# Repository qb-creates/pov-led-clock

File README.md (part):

# Persistence of Vision (POV) Clock

A propeller display that projects an image of an analog clock using a single row of LEDs. The display utilizes an ATmega32 microcontroller two 16-channel LED drivers, and a brushless DC motor.

- Project Video (YouTube): https://youtu.be/6KemDWqXEEw?si=eYfT2QDL8WkOBApL
- Persistance of Vision: https://en.wikipedia.org/wiki/Persistence_of_vision

 <div align="center">
     <!--    -->
    <!--  -->
    
 </div>

<h2> Table of Contents</h2>

1. [Software Used](#software)
2. [ESC Driver Circuit](#escdriver)
    - [PWM Overview](#escpwm)
    - [Parts List](#escpartslist) 
3. [Clock Circuit](#clockcircuit)
    - [LED Driver](#leddriver)
    - [Timer Overview](#clocktimer) 
    - [Parts List](#clockpartslist) 
4. [Power Consumption](#powerconsumption)
5. [Schematics](#schematics)
    - [ESC Driver Schematic](#escschematic)
    - [Clock Schematic](#clockschematic)
6. [STL Viewer](#stlviewer)
    - [Case Base](#casebase)
    - [Case Top](#casetop)

## 1. Software Used
- VSCode with PlatformIO extension: https://docs.platformio.org/en/latest/what-is-platformio.html
- AVRDUDE (Flash Uploader): https://github.com/avrdudes/avrdude
- KiCad (PCB Design): https://www.kicad.org
- AutoDesk Fusion 360 Personal (Case Design): https://www.autodesk.com/products/fusion-360/personal

## 2. ESC Driver Circuit
The ATtiny861 produces a PWM output that is used to drive the ESC (Electronic Speed Controller). A push button connected to PINA7 is used to adjust the duty cycle of the PWM signal.
By adjusting the duty cycle of the PWM signal to a percentage where the output is high for 1ms or less, the motor can be stopped. The push button can be pressed once to start the motor. It can be pressed
again to stop the motor. Button debouncing is accomplished in software by using a 300ms delay after detecting the first low output on the pin. The IR transmitter is used to notify
the clock circuit that it has rotated back to it's starting position. The clock circuit will start projecting the image again after it has rotated back to it's starting position. 
The inductive transmitter is  be mounted to the case while the receiver is mounted to the motor. It is connected to the clock circuit. The ESC's UBEC supplies the ATtiny, IR transmitter, 
and inductive transmitter with power (5V 3A).
<div align="center">
 <div>

 </div>
</div>

### PWM Overview
The PWM frequency is configured to be 500 Hz. The time high for a 100% duty cycle will be 2ms. Usually a 1ms pulse translates to 0% throttle and a 2ms pulse translates to 100% throttle. 
The duty cycle of the PWM signal can be adjusted by setting the Timer's OCRn register to a value between 0 and 255. Every value between 128 and 255 can be used for OCRnB without exceeding 2ms. This allows more wiggle when setting the speed of the motor instead of going from 0% throttle to 100% immediately. Calculation to find the neccessary prescaler value is shown below.

PWM Frequency Equation for ATtiny861
- PWM Frequency = fck / (prescaler * 255)
   
Variables
- fck = 16 Mhz
- Target PWM Frequency = 500 Hz
- prescaler = ?
  
Solve for prescaler
- prescaler = fck / (Target PWM Frequency * 255)
- prescaler = 16 Mhz / (500 Hz * 255)
- prescaler = 125.5 round to 128

Solve for Actual PWM Frequency
- Actual PWM Frequency = 16 Mhz / (128 * 255)
- Actual PWM Frequency = 490 Hz
---
### Parts List
|_**Part Number**_|_**Quantity**_|
|:-----|:--------:|
|<a href="https://www.digikey.com/en/products/detail/microchip-technology/ATTINY861-20PU/1245922">ATtiny861-20PU</a>| x1 |
|<a href="https://www.digikey.com/en/products/filter/rectangular-connectors/headers-male-pins/314">ISP Header</a>| x1 |
|<a href="https://www.digikey.com/en/products/filter/ceramic-capacitors/60">22pF Capacitor</a>| x2 |
|<a href="https://www.digikey.com/en/products/filter/ceramic-capacitors/60">100nF Capacitor</a>| x1 |
|<a href="https://www.digikey.com/en/products/filter/oscillators/172">16Mhz Crystal</a>| x1 |
|<a href="https://www.digikey.com/en/products/filter/through-hole-resistors/53">10K resistor</a>| x1 |
|<a href="https://www.digikey.com/en/products/filter/through-hole-resistors/53">330 resistor</a>| x1 |
|<a href="https://www.digikey.com/en/products/filter/diodes/rectifiers/single-diodes/280">1n4148 Diode</a>| x1 |
|<a href="https://www.digikey.com/en/products/detail/e-switch/RP3502ABLK/280446?s=N4IgTCBcDaIKIHECMBOADGgtAOQCIgF0BfIA">Push Button</a>| x1 |
|<a href="https://www.digikey.com/en/products/filter/rectangular-connectors/headers-male-pins/314">Pcb Board 4cm x 6cm</a>| x1 |
|<a href="https://www.amazon.com/gp/product/B08CRTR7CZ/ref=ppx_yo_dt_b_asin_title_o00_s00?ie=UTF8&psc=1">Brushless Motor</a>| x1 |
|<a href="https://www.amazon.com/gp/product/B09H5L3KN5/ref=ppx_yo_dt_b_asin_title_o02_s00?ie=UTF8&psc=1">Barrel Jack</a>| x1 |
|<a href="https://www.sparkfun.com/products/18772">Infrared Emitter</a>| x1 ||
|<a href="https://www.amazon.com/gp/product/B071GRSFBD/ref=ppx_yo_dt_b_asin_title_o03_s00?ie=UTF8&psc=1">ESC 3A UBEC</a>| x1 |
|<a href="https://www.amazon.com/Adapter-Regulated-Switching-Interchangeable-Equipment/dp/B0BFPXZ7S1/ref=sr_1_3_sspa?crid=396GU23EXCZA8&keywords=9v+power+supply&qid=1697854150&sprefix=9v+power%2Caps%2C93&sr=8-3-spons&sp_csd=d2lkZ2V0TmFtZT1zcF9hdGY&psc=1">9V 1A Power Supply</a>| x1 |
|<a href="https://www.adafruit.com/product/1407">5V 200mA Inductive Charging Set </a>| x1 |

## 3. Clock Circuit 
 This circuit projects the image of an anolog clock using of Persistence of Vision.
 The circuit is mounted to a brushless motor and will project the image of the clock everytime the
 motor completes a full rotation. An IR Detector connected to External Interrupt 0 is used to notify 
 the circuit that a full rotation of the motor has occured and that it is back at it's starting position. 
 A 2 second CTC timer is used to add one second to the clock on each CTC compare interrupt. This interrupt is 
 triggered every 1 second. Two 16 channel LED drivers are used to drive the LEDs. Communication with the LED drivers is done using the SPI protocol.
<div align="center">

</div>

### LED Drivers 
The LED Drivers are chained together. Each driver must receive two bytes of data to control their 16 output channels. Four bytes of data must be sent to the first driver in order to control all 32 output channels. The LEDs are mounted in order (starting from the center of the PCB) from 1 to 32. The table below shows which output channel each LED is connected to. 

|_**STP16CPC05 1 Outputs**_|LED Number|--|_**STP16CPC05 2 Outputs**_|LED Number|
|:--:|:--:|:--:|:--:|:--:|
|**Byte0**||--|**Byte2**||
|Out0|LED1|--|Out0|LED17|
|Out1|LED2|--|Out1|LED18|
|Out2|LED3|--|Out2|LED19|
|Out3|LED4|--|Out3|LED20|
|Out4|LED5|--|Out4|LED21|
|Out5|LED6|--|Out5|LED22|
|Out6|LED7|--|Out6|LED23|
|Out7|LED8|--|Out7|LED24|
|||--|||
|**Byte1**||--|**Byte3**||
|Out8|LED16|--|Out8|LED32|
|Out9|LED15|--|Out9|LED31|
|Out10|LED14|--|Out10|LED30|
|Out11|LED13|--|Out11|LED29|
|Out12|LED12|--|Out12|LED28|
|Out13|LED11|--|Out13|LED27|
|Out14|LED10|--|Out14|LED26|
|Out15|LED9|--|Out15|LED25|

Because the LED Drivers are daisy chained together, the data must be transmitted in the following order.
* Byte3 (MSB transmitted first) 
* Byte2 (LSB transmitted first) 
* Byte1 (MSB transmitted first) 
* Byte0 (LSB transmitted first) 
---
### Timer Overview 
A one second timer is configured to update the seconds hand of the clock. The timer is configured to operate in Clear Timer on Compare Match Mode (CTC). A CTC frequency of 0.5 Hz (2s) is required. 
This will trigger the compare match interrupt every second. Because the weight of the crystal caused the ciruit to be unbalanced, it was discarded and the ATmega32's internal 8 Mhz 
oscillator is used instead. Calculation to find the appropriate OCRn values is shown below.

CTC Waveform Frequency Equation
- Frequency = fck / (2 * prescaler * (1 + OCRnA)).

Variables
- Frequency = 0.5Hz = 2 seconds
- fck = 8 Mhz
- prescaler = 256
- OCRnA = ?

Rearranged formula to solve for OCRnA:
- OCRnA = (fck / (2 * prescaler * Frequency)) - 1

Solve for OCRnA
- OCRnA = (8 Mhz / (2 * 256 * 0.5Hz)) - 1 
- OCRnA = 31249
---
### Parts List 
|_**Part Number**_|_**Quantity**_|
|:-----|:--------:|
|<a href="https://www.mouser.com/ProductDetail/Microchip-Technology/ATMEGA32A-AU?qs=6WoM%2FY8vMbbFYDtovr%252BQ5Q%3D%3D">ATmega32A-AU</a>| x1 |
|<a href="https://www.digikey.com/en/products/filter/rectangular-connectors/headers-male-pins/314">ISP Header</a>| x1 |
|<a href="https://www.digikey.com/en/products/detail/jst-sales-america-inc/S2B-PH-SM4-TB/926655?s=N4IgTCBcDaICwFYEFoCMB2OBONyByAIiALoC%2BQA">JST Connector</a>| x1 |
|<a href="https://www.digikey.com/en/products/detail/stmicroelectronics/STP16CPC05MTR/2021162">STP16CPC05MTR LED Driver</a>| x2 |
|<a href="https://www.digikey.com/en/products/filter/led-indication-discrete/105">SMD Led 1205 (3216 Metric)</a>| x32 |
|<a href="https://www.digikey.com/en/products/filter/oscillators/172">16Mhz Crystal</a>| x1 |
|<a href="https://www.digikey.com/en/products/filter/ceramic-capacitors/60">22pF Capacitor 0603 (1608 Metric)</a>| x2 |
|<a href="https://www.digikey.com/en/products/filter/ceramic-capacitors/60">100nF Capacitor 0603 (1608 Metric)</a>| x1 |
|<a href="https://www.digikey.com/en/products/filter/through-hole-resistors/53">10K Resistor 0603 (1608 Metric)</a>| x2 |
|<a href="https://www.digikey.com/en/products/filter/through-hole-resistors/53">7.32K Resistor 0603 (1608 Metric)</a>| x2 |
|<a href="https://www.digikey.com/en/products/filter/diodes/rectifiers/single-diodes/280">1n4148 Diode</a>| x1 |
|<a href="https://www.sparkfun.com/products/19018">Infrared Detector</a>| x1 |

## 4. Power Consumption 
|_**Test Condition**_|_**Power Consumption**_|
|:--|:--:|
|Clock circuit with all LEDs powered on. LEDs are supplied with 3mA each.|120mA|
|Motor running with the weight of the clock circuit|150mA|
|Inductive charging set|100mA|
|Motor running with all LEDs powered on|380mA|

The ESC's UBEC must be able to supply at least 380mA to supply enough power to all of the components.

## 5. Schematics 
### ESC Driver Schematic
<div>
    
</div>

---
### Clock Schematic
<div>
    
</div>

## 6. STL Viewer 
### Case Base 
```stl
solid ASCII
  facet normal -9.709418e-01 2.393157e-01 0.000000e+00
    outer loop
      vertex   -7.225908e+01 -8.238542e+01 1.600000e+01
      vertex   -7.225908e+01 -8.238542e+01 3.500000e+01
      vertex   -7.140000e+01 -7.890000e+01 1.600000e+01
    endloop
  endfacet
  facet normal -9.709418e-01 2.393157e-01 0.000000e+00
    outer loop
      vertex   -7.140000e+01 -7.890000e+01 1.600000e+01
      vertex   -7.225908e+01 -8.238542e+01 3.500000e+01
      vertex   -7.140000e+01 -7.890000e+01 3.500000e+01
    endloop
  endfacet
  facet normal -9.709418e-01 -2.393157e-01 0.000000e+00
    outer loop
      vertex   -7.140000e+01 -7.890000e+01 1.600000e+01
      vertex   -7.140000e+01 -7.890000e+01 3.500000e+01
      vertex   -7.225908e+01 -7.541458e+01 1.600000e+01
    endloop
  endfacet
  facet normal -9.709418e-01 -2.393157e-01 0.000000e+00
    outer loop
      vertex   -7.225908e+01 -7.541458e+01 1.600000e+01
      vertex   -7.140000e+01 -7.890000e+01 3.500000e+01
      vertex   -7.225908e+01 -7.541458e+01 3.500000e+01
    endloop
  endfacet
  facet normal -7.485107e-01 -6.631227e-01 0.000000e+00
    outer loop
      vertex   -7.225908e+01 -7.541458e+01 1.600000e+01
      vertex   -7.225908e+01 -7.541458e+01 3.500000e+01
      vertex   -7.463951e+01 -7.272762e+01 3.500000e+01
    endloop
  endfacet
  facet normal -7.485107e-01 6.631227e-01 0.000000e+00
    outer loop
      vertex   -7.225908e+01 -8.238542e+01 1.600000e+01
      vertex   -7.463951e+01 -8.507238e+01 1.600000e+01
      vertex   -7.225908e+01 -8.238542e+01 3.500000e+01
    endloop
  endfacet
  facet normal -7.485107e-01 6.631227e-01 0.000000e+00
    outer loop
      vertex   -7.225908e+01 -8.238542e+01 3.500000e+01
      vertex   -7.463951e+01 -8.507238e+01 1.600000e+01
      vertex   -7.463951e+01 -8.507238e+01 3.500000e+01
    endloop
  endfacet
  facet normal -3.546049e-01 9.350162e-01 0.000000e+00
    outer loop
      vertex   -7.463951e+01 -8.507238e+01 3.500000e+01
      vertex   -7.463951e+01 -8.507238e+01 1.600000e+01
      vertex   -7.799597e+01 -8.634532e+01 1.600000e+01
    endloop
  endfacet
  facet normal -3.546049e-01 9.350162e-01 0.000000e+00
    outer loop
      vertex   -7.463951e+01 -8.507238e+01 3.500000e+01
      vertex   -7.799597e+01 -8.634532e+01 1.600000e+01
      vertex   -7.799597e+01 -8.634532e+01 3.500000e+01
    endloop
  endfacet
  facet normal 1.205367e-01 9.927089e-01 0.000000e+00
    outer loop
      vertex   -7.799597e+01 -8.634532e+01 3.500000e+01
      vertex   -7.799597e+01 -8.634532e+01 1.600000e+01
      vertex   -8.155954e+01 -8.591262e+01 1.600000e+01
    endloop
  endfacet
  facet normal 1.205367e-01 9.927089e-01 0.000000e+00
    outer loop
      vertex   -7.799597e+01 -8.634532e+01 3.500000e+01
      vertex   -8.155954e+01 -8.591262e+01 1.600000e+01
      vertex   -8.155954e+01 -8.591262e+01 3.500000e+01
    endloop
  endfacet
  facet normal 5.680647e-01 8.229839e-01 0.000000e+00
    outer loop
      vertex   -8.155954e+01 -8.591262e+01 3.500000e+01
      vertex   -8.155954e+01 -8.591262e+01 1.600000e+01
      vertex   -8.451383e+01 -8.387342e+01 1.600000e+01
    endloop
  endfacet
  facet normal 5.680647e-01 8.229839e-01 -4.297325e-16
    outer loop
      vertex   -8.155954e+01 -8.591262e+01 3.500000e+01
      vertex   -8.451383e+01 -8.387342e+01 1.600000e+01
      vertex   -8.451383e+01 -8.387342e+01 3.500000e+01
    endloop
  endfacet
  facet normal 8.854560e-01 4.647232e-01 -6.622677e-16
    outer loop
      vertex   -8.451383e+01 -8.387342e+01 3.500000e+01
      vertex   -8.451383e+01 -8.387342e+01 1.600000e+01
      vertex   -8.618206e+01 -8.069487e+01 1.600000e+01
    endloop
  endfacet
  facet normal 8.854560e-01 4.647232e-01 0.000000e+00
    outer loop
      vertex   -8.451383e+01 -8.387342e+01 3.500000e+01
      vertex   -8.618206e+01 -8.069487e+01 1.600000e+01
      vertex   -8.618206e+01 -8.069487e+01 3.500000e+01
    endloop
  endfacet
  facet normal 1.000000e+00 0.000000e+00 0.000000e+00
    outer loop
      vertex   -8.618206e+01 -8.069487e+01 3.500000e+01
      vertex   -8.618206e+01 -8.069487e+01 1.600000e+01
      vertex   -8.618206e+01 -7.710513e+01 1.600000e+01
    endloop
  endfacet
  facet normal 1.000000e+00 -0.000000e+00 0.000000e+00
    outer loop
      vertex   -8.618206e+01 -8.069487e+01 3.500000e+01
      vertex   -8.618206e+01 -7.710513e+01 1.600000e+01
      vertex   -8.618206e+01 -7.710513e+01 3.500000e+01
    endloop
  endfacet
  facet normal 8.854560e-01 -4.647232e-01 -3.475849e-16
    outer loop
      vertex   -8.618206e+01 -7.710513e+01 3.500000e+01
      vertex   -8.618206e+01 -7.710513e+01 1.600000e+01
      vertex   -8.451383e+01 -7.392658e+01 1.600000e+01
    endloop
  endfacet
  facet normal 8.854560e-01 -4.647232e-01 3.125327e-16
    outer loop
      vertex   -8.618206e+01 -7.710513e+01 3.500000e+01
      vertex   -8.451383e+01 -7.392658e+01 1.600000e+01
      vertex   -8.451383e+01 -7.392658e+01 3.500000e+01
    endloop
  endfacet
  facet normal 5.680647e-01 -8.229839e-01 -1.906641e-16
    outer loop
      vertex   -8.451383e+01 -7.392658e+01 3.500000e+01
      vertex   -8.451383e+01 -7.392658e+01 1.600000e+01
      vertex   -8.155954e+01 -7.188738e+01 1.600000e+01
    endloop
  endfacet
  facet normal 5.680647e-01 -8.229839e-01 0.000000e+00
    outer loop
      vertex   -8.451383e+01 -7.392658e+01 3.500000e+01
      vertex   -8.155954e+01 -7.188738e+01 1.600000e+01
      vertex   -8.155954e+01 -7.188738e+01 3.500000e+01
    endloop
  endfacet
  facet normal 1.205367e-01 -9.927089e-01 0.000000e+00
    outer loop
      vertex   -8.155954e+01 -7.188738e+01 3.500000e+01
      vertex   -8.155954e+01 -7.188738e+01 1.600000e+01
      vertex   -7.799597e+01 -7.145468e+01 1.600000e+01
    endloop
  endfacet
  facet normal 1.205367e-01 -9.927089e-01 0.000000e+00
    outer loop
      vertex   -8.155954e+01 -7.188738e+01 3.500000e+01
      vertex   -7.799597e+01 -7.145468e+01 1.600000e+01
      vertex   -7.799597e+01 -7.145468e+01 3.500000e+01
    endloop
  endfacet
  facet normal -3.546049e-01 -9.350162e-01 -0.000000e+00
    outer loop
      vertex   -7.799597e+01 -7.145468e+01 3.500000e+01
      vertex   -7.799597e+01 -7.145468e+01 1.600000e+01
      vertex   -7.463951e+01 -7.272762e+01 1.600000e+01
    endloop
  endfacet
  facet normal -3.546049e-01 -9.350162e-01 0.000000e+00
    outer loop
      vertex   -7.799597e+01 -7.145468e+01 3.500000e+01
      vertex   -7.463951e+01 -7.272762e+01 1.600000e+01
      vertex   -7.463951e+01 -7.272762e+01 3.500000e+01
    endloop
  endfacet
  facet normal -7.485107e-01 -6.631227e-01 -0.000000e+00
    outer loop
      vertex   -7.463951e+01 -7.272762e+01 3.500000e+01
      vertex   -7.463951e+01 -7.272762e+01 1.600000e+01
      vertex   -7.225908e+01 -7.541458e+01 1.600000e+01
    endloop
  endfacet
  facet normal -1.000000e+00 0.000000e+00 0.000000e+00
    outer loop
      vertex   -8.890000e+01 -8.890000e+01 3.500000e+01
      vertex   -8.890000e+01 8.890000e+01 3.500000e+01
      vertex   -8.890000e+01 -8.890000e+01 0.000000e+00
    endloop
  endfacet
  facet normal -1.000000e+00 0.000000e+00 0.000000e+00
    outer loop
      vertex   -8.890000e+01 -8.890000e+01 0.000000e+00
      vertex   -8.890000e+01 8.890000e+01 3.500000e+01
      vertex   -8.890000e+01 8.890000e+01 0.000000e+00
    endloop
  endfacet
  facet normal -9.709418e-01 2.393157e-01 0.000000e+00
    outer loop
      vertex   -7.225908e+01 7.541458e+01 1.600000e+01
      vertex   -7.225908e+01 7.541458e+01 3.500000e+01
      vertex   -7.140000e+01 7.890000e+01 1.600000e+01
    endloop
  endfacet
  facet normal -9.709418e-01 2.393157e-01 0.000000e+00
    outer loop
      vertex   -7.140000e+01 7.890000e+01 1.600000e+01
      vertex   -7.225908e+01 7.541458e+01 3.500000e+01
      vertex   -7.140000e+01 7.890000e+01 3.500000e+01
    endloop
  endfacet
  facet normal -9.709418e-01 -2.393157e-01 0.000000e+00
    outer loop
      vertex   -7.140000e+01 7.890000e+01 1.600000e+01
      vertex   -7.140000e+01 7.890000e+01 3.500000e+01
      vertex   -7.225908e+01 8.238542e+01 1.600000e+01
    endloop
  endfacet
  facet normal -9.709418e-01 -2.393157e-01 0.000000e+00
    outer loop
      vertex   -7.225908e+01 8.238542e+01 1.600000e+01
      vertex   -7.140000e+01 7.890000e+01 3.500000e+01
      vertex   -7.225908e+01 8.238542e+01 3.500000e+01
    endloop
  endfacet
  facet normal -7.485107e-01 -6.631227e-01 0.000000e+00
    outer loop
      vertex   -7.225908e+01 8.238542e+01 1.600000e+01
      vertex   -7.225908e+01 8.238542e+01 3.500000e+01
      vertex   -7.463951e+01 8.507238e+01 3.500000e+01
    endloop
  endfacet
  facet normal -7.485107e-01 6.631227e-01 0.000000e+00
    outer loop
      vertex   -7.225908e+01 7.541458e+01 1.600000e+01
      vertex   -7.463951e+01 7.272762e+01 1.600000e+01
      vertex   -7.225908e+01 7.541458e+01 3.500000e+01
    endloop
  endfacet
  facet normal -7.485107e-01 6.631227e-01 0.000000e+00
    outer loop
      vertex   -7.225908e+01 7.541458e+01 3.500000e+01
      vertex   -7.463951e+01 7.272762e+01 1.600000e+01
      vertex   -7.463951e+01 7.272762e+01 3.500000e+01
    endloop
  endfacet
  facet normal -3.546049e-01 9.350162e-01 0.000000e+00
    outer loop
      vertex   -7.463951e+01 7.272762e+01 3.500000e+01
      vertex   -7.463951e+01 7.272762e+01 1.600000e+01
      vertex   -7.799597e+01 7.145468e+01 1.600000e+01
    endloop
  endfacet
  facet normal -3.546049e-01 9.350162e-01 0.000000e+00
    outer loop
      vertex   -7.463951e+01 7.272762e+01 3.500000e+01
      vertex   -7.799597e+01 7.145468e+01 1.600000e+01
      vertex   -7.799597e+01 7.145468e+01 3.500000e+01
    endloop
  endfacet
  facet normal 1.205367e-01 9.927089e-01 0.000000e+00
    outer loop
      vertex   -7.799597e+01 7.145468e+01 3.500000e+01
      vertex   -7.799597e+01 7.145468e+01 1.600000e+01
      vertex   -8.155954e+01 7.188738e+01 1.600000e+01
    endloop
  endfacet
  facet normal 1.205367e-01 9.927089e-01 0.000000e+00
    outer loop
      vertex   -7.799597e+01 7.145468e+01 3.500000e+01
      vertex   -8.155954e+01 7.188738e+01 1.600000e+01
      vertex   -8.155954e+01 7.188738e+01 3.500000e+01
    endloop
  endfacet
  facet normal 5.680647e-01 8.229839e-01 0.000000e+00
    outer loop
      vertex   -8.155954e+01 7.188738e+01 3.500000e+01
      vertex   -8.155954e+01 7.188738e+01 1.600000e+01
      vertex   -8.451383e+01 7.392658e+01 1.600000e+01
    endloop
  endfacet
  facet normal 5.680647e-01 8.229839e-01 1.953329e-16
    outer loop
      vertex   -8.155954e+01 7.188738e+01 3.500000e+01
      vertex   -8.451383e+01 7.392658e+01 1.600000e+01
      vertex   -8.451383e+01 7.392658e+01 3.500000e+01
    endloop
  endfacet
  facet normal 8.854560e-01 4.647232e-01 -3.146828e-16
    outer loop
      vertex   -8.451383e+01 7.392658e+01 3.500000e+01
      vertex   -8.451383e+01 7.392658e+01 1.600000e+01
      vertex   -8.618206e+01 7.710513e+01 1.600000e+01
    endloop
  endfacet
  facet normal 8.854560e-01 4.647232e-01 3.385771e-16
    outer loop
      vertex   -8.451383e+01 7.392658e+01 3.500000e+01
      vertex   -8.618206e+01 7.710513e+01 1.600000e+01
      vertex   -8.618206e+01 7.710513e+01 3.500000e+01
    endloop
  endfacet
  facet normal 1.000000e+00 0.000000e+00 0.000000e+00
    outer loop
      vertex   -8.618206e+01 7.710513e+01 3.500000e+01
      vertex   -8.618206e+01 7.710513e+01 1.600000e+01
      vertex   -8.618206e+01 8.069487e+01 1.600000e+01
    endloop
  endfacet
  facet normal 1.000000e+00 -0.000000e+00 0.000000e+00
    outer loop
      vertex   -8.618206e+01 7.710513e+01 3.500000e+01
      vertex   -8.618206e+01 8.069487e+01 1.600000e+01
      vertex   -8.618206e+01 8.069487e+01 3.500000e+01
    endloop
  endfacet
  facet normal 8.854560e-01 -4.647232e-01 0.000000e+00
    outer loop
      vertex   -8.618206e+01 8.069487e+01 3.500000e+01
      vertex   -8.618206e+01 8.069487e+01 1.600000e+01
      vertex   -8.451383e+01 8.387342e+01 1.600000e+01
    endloop
  endfacet
  facet normal 8.854560e-01 -4.647232e-01 6.641320e-16
    outer loop
      vertex   -8.618206e+01 8.069487e+01 3.500000e+01
      vertex   -8.451383e+01 8.387342e+01 1.600000e+01
      vertex   -8.451383e+01 8.387342e+01 3.500000e+01
    endloop
  endfacet
  facet normal 5.680647e-01 -8.229839e-01 4.248782e-16
    outer loop
      vertex   -8.451383e+01 8.387342e+01 3.500000e+01
      vertex   -8.451383e+01 8.387342e+01 1.600000e+01
      vertex   -8.155954e+01 8.591262e+01 1.600000e+01
    endloop
  endfacet
  facet normal 5.680647e-01 -8.229839e-01 0.000000e+00
    outer loop
      vertex   -8.451383e+01 8.387342e+01 3.500000e+01
      vertex   -8.155954e+01 8.591262e+01 1.600000e+01
      vertex   -8.155954e+01 8.591262e+01 3.500000e+01
    endloop
  endfacet
  facet normal 1.205367e-01 -9.927089e-01 0.000000e+00
    outer loop
      vertex   -8.155954e+01 8.591262e+01 3.500000e+01
      vertex   -8.155954e+01 8.591262e+01 1.600000e+01
      vertex   -7.799597e+01 8.634532e+01 1.600000e+01
    endloop
  endfacet
  facet normal 1.205367e-01 -9.927089e-01 0.000000e+00
    outer loop
      vertex   -8.155954e+01 8.591262e+01 3.500000e+01
      vertex   -7.799597e+01 8.634532e+01 1.600000e+01
      vertex   -7.799597e+01 8.634532e+01 3.500000e+01
    endloop
  endfacet
  facet normal -3.546049e-01 -9.350162e-01 -0.000000e+00
    outer loop
      vertex   -7.799597e+01 8.634532e+01 3.500000e+01
      vertex   -7.799597e+01 8.634532e+01 1.600000e+01
      vertex   -7.463951e+01 8.507238e+01 1.600000e+01
    endloop
  endfacet
  facet normal -3.546049e-01 -9.350162e-01 0.000000e+00
    outer loop
      vertex   -7.799597e+01 8.634532e+01 3.500000e+01
      vertex   -7.463951e+01 8.507238e+01 1.600000e+01
      vertex   -7.463951e+01 8.507238e+01 3.500000e+01
    endloop
  endfacet
  facet normal -7.485107e-01 -6.631227e-01 -0.000000e+00
    outer loop
      vertex   -7.463951e+01 8.507238e+01 3.500000e+01
      vertex   -7.463951e+01 8.507238e+01 1.600000e+01
      vertex   -7.225908e+01 8.238542e+01 1.600000e+01
    endloop
  endfacet
  facet normal -0.000000e+00 1.000000e+00 0.000000e+00
    outer loop
      vertex   -8.890000e+01 8.890000e+01 3.500000e+01
      vertex   8.890000e+01 8.890000e+01 3.500000e+01
      vertex   -8.890000e+01 8.890000e+01 0.000000e+00
    endloop
  endfacet
  facet normal 0.000000e+00 1.000000e+00 0.000000e+00
    outer loop
      vertex   -8.890000e+01 8.890000e+01 0.000000e+00
      vertex   8.890000e+01 8.890000e+01 3.500000e+01
      vertex   8.890000e+01 8.890000e+01 0.000000e+00
    endloop
  endfacet
  facet normal -9.709418e-01 2.393157e-01 0.000000e+00
    outer loop
      vertex   8.554092e+01 -8.238542e+01 1.600000e+01
      vertex   8.554092e+01 -8.238542e+01 3.500000e+01
      vertex   8.640000e+01 -7.890000e+01 1.600000e+01
    endloop
  endfacet
  facet normal -9.709418e-01 2.393157e-01 0.000000e+00
    outer loop
      vertex   8.640000e+01 -7.890000e+01 1.600000e+01
      vertex   8.554092e+01 -8.238542e+01 3.500000e+01
      vertex   8.640000e+01 -7.890000e+01 3.500000e+01
    endloop
  endfacet
  facet normal -9.709418e-01 -2.393157e-01 0.000000e+00
    outer loop
      vertex   8.640000e+01 -7.890000e+01 1.600000e+01
      vertex   8.640000e+01 -7.890000e+01 3.500000e+01
      vertex   8.554092e+01 -7.541458e+01 1.600000e+01
    endloop
  endfacet
  facet normal -9.709418e-01 -2.393157e-01 0.000000e+00
    outer loop
      vertex   8.554092e+01 -7.541458e+01 1.600000e+01
      vertex   8.640000e+01 -7.890000e+01 3.500000e+01
      vertex   8.554092e+01 -7.541458e+01 3.500000e+01
    endloop
  endfacet
  facet normal -7.485107e-01 -6.631227e-01 0.000000e+00
    outer loop
      vertex   8.554092e+01 -7.541458e+01 1.600000e+01
      vertex   8.554092e+01 -7.541458e+01 3.500000e+01
      vertex   8.316049e+01 -7.272762e+01 3.500000e+01
    endloop
  endfacet
  facet normal -7.485107e-01 6.631227e-01 0.000000e+00
    outer loop
      vertex   8.554092e+01 -8.238542e+01 1.600000e+01
      vertex   8.316049e+01 -8.507238e+01 1.600000e+01
      vertex   8.554092e+01 -8.238542e+01 3.500000e+01
    endloop
  endfacet
  facet normal -7.485107e-01 6.631227e-01 0.000000e+00
    outer loop
      vertex   8.554092e+01 -8.238542e+01 3.500000e+01
      vertex   8.316049e+01 -8.507238e+01 1.600000e+01
      vertex   8.316049e+01 -8.507238e+01 3.500000e+01
    endloop
  endfacet
  facet normal -3.546049e-01 9.350162e-01 0.000000e+00
    outer loop
      vertex   8.316049e+01 -8.507238e+01 3.500000e+01
      vertex   8.316049e+01 -8.507238e+01 1.600000e+01
      vertex   7.980403e+01 -8.634532e+01 1.600000e+01
    endloop
  endfacet
  facet normal -3.546049e-01 9.350162e-01 0.000000e+00
    outer loop
      vertex   8.316049e+01 -8.507238e+01 3.500000e+01
      vertex   7.980403e+01 -8.634532e+01 1.600000e+01
      vertex   7.980403e+01 -8.634532e+01 3.500000e+01
    endloop
  endfacet
  facet normal 1.205367e-01 9.927089e-01 0.000000e+00
    outer loop
      vertex   7.980403e+01 -8.634532e+01 3.500000e+01
      vertex   7.980403e+01 -8.634532e+01 1.600000e+01
      vertex   7.624046e+01 -8.591262e+01 1.600000e+01
    endloop
  endfacet
  facet normal 1.205367e-01 9.927089e-01 0.000000e+00
    outer loop
      vertex   7.980403e+01 -8.634532e+01 3.500000e+01
      vertex   7.624046e+01 -8.591262e+01 1.600000e+01
      vertex   7.624046e+01 -8.591262e+01 3.500000e+01
    endloop
  endfacet
  facet normal 5.680647e-01 8.229839e-01 0.000000e+00
    outer loop
      vertex   7.624046e+01 -8.591262e+01 3.500000e+01
      vertex   7.624046e+01 -8.591262e+01 1.600000e+01
      vertex   7.328617e+01 -8.387342e+01 1.600000e+01
    endloop
  endfacet
  facet normal 5.680647e-01 8.229839e-01 0.000000e+00
    outer loop
      vertex   7.624046e+01 -8.591262e+01 3.500000e+01
      vertex   7.328617e+01 -8.387342e+01 1.600000e+01
      vertex   7.328617e+01 -8.387342e+01 3.500000e+01
    endloop
  endfacet
  facet normal 8.854560e-01 4.647232e-01 0.000000e+00
    outer loop
      vertex   7.328617e+01 -8.387342e+01 3.500000e+01
      vertex   7.328617e+01 -8.387342e+01 1.600000e+01
      vertex   7.161794e+01 -8.069487e+01 1.600000e+01
    endloop
  endfacet
  facet normal 8.854560e-01 4.647232e-01 0.000000e+00
    outer loop
      vertex   7.328617e+01 -8.387342e+01 3.500000e+01
      vertex   7.161794e+01 -8.069487e+01 1.600000e+01
      vertex   7.161794e+01 -8.069487e+01 3.500000e+01
    endloop
  endfacet
  facet normal 1.000000e+00 0.000000e+00 0.000000e+00
    outer loop
      vertex   7.161794e+01 -8.069487e+01 3.500000e+01
      vertex   7.161794e+01 -8.069487e+01 1.600000e+01
      vertex   7.161794e+01 -7.710513e+01 1.600000e+01
    endloop
  endfacet
  facet normal 1.000000e+00 -0.000000e+00 0.000000e+00
    outer loop
      vertex   7.161794e+01 -8.069487e+01 3.500000e+01
      vertex   7.161794e+01 -7.710513e+01 1.600000e+01
      vertex   7.161794e+01 -7.710513e+01 3.500000e+01
    endloop
  endfacet
  facet normal 8.854560e-01 -4.647232e-01 -3.475849e-16
    outer loop
      vertex   7.161794e+01 -7.710513e+01 3.500000e+01
      vertex   7.161794e+01 -7.710513e+01 1.600000e+01
      vertex   7.328617e+01 -7.392658e+01 1.600000e+01
    endloop
  endfacet
  facet normal 8.854560e-01 -4.647232e-01 -3.515993e-16
    outer loop
      vertex   7.161794e+01 -7.710513e+01 3.500000e+01
      vertex   7.328617e+01 -7.392658e+01 1.600000e+01
      vertex   7.328617e+01 -7.392658e+01 3.500000e+01
    endloop
  endfacet
  facet normal 5.680647e-01 -8.229839e-01 -6.155423e-16
    outer loop
      vertex   7.328617e+01 -7.392658e+01 3.500000e+01
      vertex   7.328617e+01 -7.392658e+01 1.600000e+01
      vertex   7.624046e+01 -7.188738e+01 1.600000e+01
    endloop
  endfacet
  facet normal 5.680647e-01 -8.229839e-01 0.000000e+00
    outer loop
      vertex   7.328617e+01 -7.392658e+01 3.500000e+01
      vertex   7.624046e+01 -7.188738e+01 1.600000e+01
      vertex   7.624046e+01 -7.188738e+01 3.500000e+01
    endloop
  endfacet
  facet normal 1.205367e-01 -9.927089e-01 0.000000e+00
    outer loop
      vertex   7.624046e+01 -7.188738e+01 3.500000e+01
      vertex   7.624046e+01 -7.188738e+01 1.600000e+01
      vertex   7.980403e+01 -7.145468e+01 1.600000e+01
    endloop
  endfacet
  facet normal 1.205367e-01 -9.927089e-01 0.000000e+00
    outer loop
      vertex   7.624046e+01 -7.188738e+01 3.500000e+01
      vertex   7.980403e+01 -7.145468e+01 1.600000e+01
      vertex   7.980403e+01 -7.145468e+01 3.500000e+01
    endloop
  endfacet
  facet normal -3.546049e-01 -9.350162e-01 -0.000000e+00
    outer loop
      vertex   7.980403e+01 -7.145468e+01 3.500000e+01
      vertex   7.980403e+01 -7.145468e+01 1.600000e+01
      vertex   8.316049e+01 -7.272762e+01 1.600000e+01
    endloop
  endfacet
  facet normal -3.546049e-01 -9.350162e-01 0.000000e+00
    outer loop
      vertex   7.980403e+01 -7.145468e+01 3.500000e+01
      vertex   8.316049e+01 -7.272762e+01 1.600000e+01
      vertex   8.316049e+01 -7.272762e+01 3.500000e+01
    endloop
  endfacet
  facet normal -7.485107e-01 -6.631227e-01 -0.000000e+00
    outer loop
      vertex   8.316049e+01 -7.272762e+01 3.500000e+01
      vertex   8.316049e+01 -7.272762e+01 1.600000e+01
      vertex   8.554092e+01 -7.541458e+01 1.600000e+01
    endloop
  endfacet
  facet normal -0.000000e+00 0.000000e+00 -1.000000e+00
    outer loop
      vertex   -8.554092e+01 -8.238542e+01 0.000000e+00
      vertex   -8.890000e+01 -8.890000e+01 0.000000e+00
      vertex   -8.640000e+01 -7.890000e+01 0.000000e+00
    endloop
  endfacet
  facet normal -0.000000e+00 0.000000e+00 -1.000000e+00
    outer loop
      vertex   -8.640000e+01 -7.890000e+01 0.000000e+00
      vertex   -8.890000e+01 -8.890000e+01 0.000000e+00
      vertex   -8.640000e+01 7.890000e+01 0.000000e+00
    endloop
  endfacet
  facet normal 0.000000e+00 0.000000e+00 -1.000000e+00
    outer loop
      vertex   -8.640000e+01 -7.890000e+01 0.000000e+00
      vertex   -8.640000e+01 7.890000e+01 0.000000e+00
      vertex   -8.554092e+01 -7.541458e+01 0.000000e+00
    endloop
  endfacet
  facet normal 0.000000e+00 0.000000e+00 -1.000000e+00
    outer loop
      vertex   -8.554092e+01 -7.541458e+01 0.000000e+00
      vertex   -8.640000e+01 7.890000e+01 0.000000e+00
      vertex   -8.554092e+01 7.541458e+01 0.000000e+00
    endloop
  endfacet
  facet normal 0.000000e+00 0.000000e+00 -1.000000e+00
    outer loop
      vertex   -8.554092e+01 -7.541458e+01 0.000000e+00
      vertex   -8.554092e+01 7.541458e+01 0.000000e+00
      vertex   -8.316049e+01 7.272762e+01 0.000000e+00
    endloop
  endfacet
  facet normal 0.000000e+00 -0.000000e+00 -1.000000e+00
    outer loop
      vertex   -8.554092e+01 -8.238542e+01 0.000000e+00
      vertex   -8.316049e+01 -8.507238e+01 0.000000e+00
      vertex   -8.890000e+01 -8.890000e+01 0.000000e+00
    endloop
  endfacet
  facet normal 0.000000e+00 0.000000e+00 -1.000000e+00
    outer loop
      vertex   -8.890000e+01 -8.890000e+01 0.000000e+00
      vertex   -8.316049e+01 -8.507238e+01 0.000000e+00
      vertex   -7.980403e+01 -8.634532e+01 0.000000e+00
    endloop
  endfacet
  facet normal 0.000000e+00 0.000000e+00 -1.000000e+00
    outer loop
      vertex   -8.890000e+01 -8.890000e+01 0.000000e+00
      vertex   -7.980403e+01 -8.634532e+01 0.000000e+00
      vertex   -7.624046e+01 -8.591262e+01 0.000000e+00
    endloop
  endfacet
  facet normal 0.000000e+00 -0.000000e+00 -1.000000e+00
    outer loop
      vertex   -7.328617e+01 -8.387342e+01 0.000000e+00
      vertex   7.463951e+01 -8.507238e+01 0.000000e+00
      vertex   -7.624046e+01 -8.591262e+01 0.000000e+00
    endloop
  endfacet
  facet normal 0.000000e+00 0.000000e+00 -1.000000e+00
    outer loop
      vertex   -7.624046e+01 -8.591262e+01 0.000000e+00
      vertex   7.463951e+01 -8.507238e+01 0.000000e+00
      vertex   7.799597e+01 -8.634532e+01 0.000000e+00
    endloop
  endfacet
  facet normal 0.000000e+00 -0.000000e+00 -1.000000e+00
    outer loop
      vertex   -7.624046e+01 -8.591262e+01 0.000000e+00
      vertex   7.799597e+01 -8.634532e+01 0.000000e+00
      vertex   -8.890000e+01 -8.890000e+01 0.000000e+00
    endloop
  endfacet
  facet normal 0.000000e+00 0.000000e+00 -1.000000e+00
    outer loop
      vertex   -8.890000e+01 -8.890000e+01 0.000000e+00
      vertex   7.799597e+01 -8.634532e+01 0.000000e+00
      vertex   8.890000e+01 -8.890000e+01 0.000000e+00
    endloop
  endfacet
  facet normal 0.000000e+00 0.000000e+00 -1.000000e+00
    outer loop
      vertex   8.890000e+01 -8.890000e+01 0.000000e+00
      vertex   7.799597e+01 -8.634532e+01 0.000000e+00
      vertex   8.155954e+01 -8.591262e+01 0.000000e+00
    endloop
  endfacet
  facet normal 0.000000e+00 0.000000e+00 -1.000000e+00
    outer loop
      vertex   8.890000e+01 -8.890000e+01 0.000000e+00
      vertex   8.155954e+01 -8.591262e+01 0.000000e+00
      vertex   8.451383e+01 -8.387342e+01 0.000000e+00
    endloop
  endfacet
  facet normal 0.000000e+00 0.000000e+00 -1.000000e+00
    outer loop
      vertex   7.463951e+01 -8.507238e+01 0.000000e+00
      vertex   -7.328617e+01 -8.387342e+01 0.000000e+00
      vertex   7.225908e+01 -8.238542e+01 0.000000e+00
    endloop
  endfacet
  facet normal -0.000000e+00 0.000000e+00 -1.000000e+00
    outer loop
      vertex   7.225908e+01 -8.238542e+01 0.000000e+00
      vertex   -7.328617e+01 -8.387342e+01 0.000000e+00
      vertex   -7.161794e+01 -8.069487e+01 0.000000e+00
    endloop
  endfacet
  facet normal 0.000000e+00 0.000000e+00 -1.000000e+00
    outer loop
      vertex   7.225908e+01 -8.238542e+01 0.000000e+00
      vertex   -7.161794e+01 -8.069487e+01 0.000000e+00
      vertex   7.140000e+01 -7.890000e+01 0.000000e+00
    endloop
  endfacet
  facet normal -0.000000e+00 0.000000e+00 -1.000000e+00
    outer loop
      vertex   7.140000e+01 -7.890000e+01 0.000000e+00
      vertex   -7.161794e+01 -8.069487e+01 0.000000e+00
      vertex   -1.291757e+00 -1.394028e+01 0.000000e+00
    endloop
  endfacet
  facet normal 0.000000e+00 0.000000e+00 -1.000000e+00
    outer loop
      vertex   7.140000e+01 -7.890000e+01 0.000000e+00
      vertex   -1.291757e+00 -1.394028e+01 0.000000e+00
      vertex   3.831282e+00 -1.346556e+01 0.000000e+00
    endloop
  endfacet
  facet normal 0.000000e+00 0.000000e+00 -1.000000e+00
    outer loop
      vertex   -7.161794e+01 -8.069487e+01 0.000000e+00
      vertex   -7.161794e+01 -7.710513e+01 0.000000e+00
      vertex   -1.291757e+00 -1.394028e+01 0.000000e+00
    endloop
  endfacet
  facet normal -0.000000e+00 0.000000e+00 -1.000000e+00
    outer loop
      vertex   -1.291757e+00 -1.394028e+01 0.000000e+00
      vertex   -7.161794e+01 -7.710513e+01 0.000000e+00
      vertex   -6.240337e+00 -1.253229e+01 0.000000e+00
    endloop
  endfacet
  facet normal 0.000000e+00 0.000000e+00 -1.000000e+00
    outer loop
      vertex   -6.240337e+00 -1.253229e+01 0.000000e+00
      vertex   -7.161794e+01 -7.710513e+01 0.000000e+00
      vertex   -7.328617e+01 -7.392658e+01 0.000000e+00
    endloop
  endfacet
  facet normal -0.000000e+00 0.000000e+00 -1.000000e+00
    outer loop
      vertex   -6.240337e+00 -1.253229e+01 0.000000e+00
      vertex   -7.328617e+01 -7.392658e+01 0.000000e+00
      vertex   -1.034612e+01 -9.431739e+00 0.000000e+00
    endloop
  endfacet
  facet normal 0.000000e+00 0.000000e+00 -1.000000e+00
    outer loop
      vertex   -1.034612e+01 -9.431739e+00 0.000000e+00
      vertex   -7.328617e+01 -7.392658e+01 0.000000e+00
      vertex   -7.624046e+01 -7.188738e+01 0.000000e+00
    endloop
  endfacet
  facet normal -0.000000e+00 0.000000e+00 -1.000000e+00
    outer loop
      vertex   -1.034612e+01 -9.431739e+00 0.000000e+00
      vertex   -7.624046e+01 -7.188738e+01 0.000000e+00
      vertex   -1.305461e+01 -5.057383e+00 0.000000e+00
    endloop
  endfacet
  facet normal 0.000000e+00 0.000000e+00 -1.000000e+00
    outer loop
      vertex   -1.305461e+01 -5.057383e+00 0.000000e+00
      vertex   -7.624046e+01 -7.188738e+01 0.000000e+00
      vertex   -7.980403e+01 -7.145468e+01 0.000000e+00
    endloop
  endfacet
  facet normal -0.000000e+00 0.000000e+00 -1.000000e+00
    outer loop
      vertex   -1.305461e+01 -5.057383e+00 0.000000e+00
      vertex   -7.980403e+01 -7.145468e+01 0.000000e+00
      vertex   -1.400000e+01 1.714506e-15 0.000000e+00
    endloop
  endfacet
  facet normal -0.000000e+00 0.000000e+00 -1.000000e+00
    outer loop
      vertex   -1.400000e+01 1.714506e-15 0.000000e+00
      vertex   -7.980403e+01 -7.145468e+01 0.000000e+00
      vertex   -7.980403e+01 7.145468e+01 0.000000e+00
    endloop
  endfacet
  facet normal 0.000000e+00 0.000000e+00 -1.000000e+00
    outer loop
      vertex   -1.400000e+01 1.714506e-15 0.000000e+00
      vertex   -7.980403e+01 7.145468e+01 0.000000e+00
      vertex   -1.305461e+01 5.057383e+00 0.000000e+00
    endloop
  endfacet
  facet normal 0.000000e+00 0.000000e+00 -1.000000e+00
    outer loop
      vertex   -1.305461e+01 5.057383e+00 0.000000e+00
      vertex   -7.980403e+01 7.145468e+01 0.000000e+00
      vertex   -7.624046e+01 7.188738e+01 0.000000e+00
    endloop
  endfacet
  facet normal 0.000000e+00 0.000000e+00 -1.000000e+00
    outer loop
      vertex   -1.305461e+01 5.057383e+00 0.000000e+00
      vertex   -7.624046e+01 7.188738e+01 0.000000e+00
      vertex   -1.034612e+01 9.431739e+00 0.000000e+00
    endloop
  endfacet
  facet normal 0.000000e+00 0.000000e+00 -1.000000e+00
    outer loop
      vertex   -1.034612e+01 9.431739e+00 0.000000e+00
      vertex   -7.624046e+01 7.188738e+01 0.000000e+00
      vertex   -7.328617e+01 7.392658e+01 0.000000e+00
    endloop
  endfacet
  facet normal 0.000000e+00 0.000000e+00 -1.000000e+00
    outer loop
      vertex   -1.034612e+01 9.431739e+00 0.000000e+00
      vertex   -7.328617e+01 7.392658e+01 0.000000e+00
      vertex   -6.240337e+00 1.253229e+01 0.000000e+00
    endloop
  endfacet
  facet normal 0.000000e+00 0.000000e+00 -1.000000e+00
    outer loop
      vertex   -6.240337e+00 1.253229e+01 0.000000e+00
      vertex   -7.328617e+01 7.392658e+01 0.000000e+00
      vertex   -7.161794e+01 7.710513e+01 0.000000e+00
    endloop
  endfacet
  facet normal 0.000000e+00 0.000000e+00 -1.000000e+00
    outer loop
      vertex   -6.240337e+00 1.253229e+01 0.000000e+00
      vertex   -7.161794e+01 7.710513e+01 0.000000e+00
      vertex   -1.291757e+00 1.394028e+01 0.000000e+00
    endloop
  endfacet
  facet normal 0.000000e+00 0.000000e+00 -1.000000e+00
    outer loop
      vertex   -1.291757e+00 1.394028e+01 0.000000e+00
      vertex   -7.161794e+01 7.710513e+01 0.000000e+00
      vertex   -7.161794e+01 8.069487e+01 0.000000e+00
    endloop
  endfacet
  facet normal 0.000000e+00 0.000000e+00 -1.000000e+00
    outer loop
      vertex   -1.291757e+00 1.394028e+01 0.000000e+00
      vertex   -7.161794e+01 8.069487e+01 0.000000e+00
      vertex   7.140000e+01 7.890000e+01 0.000000e+00
    endloop
  endfacet
  facet normal 0.000000e+00 0.000000e+00 -1.000000e+00
    outer loop
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
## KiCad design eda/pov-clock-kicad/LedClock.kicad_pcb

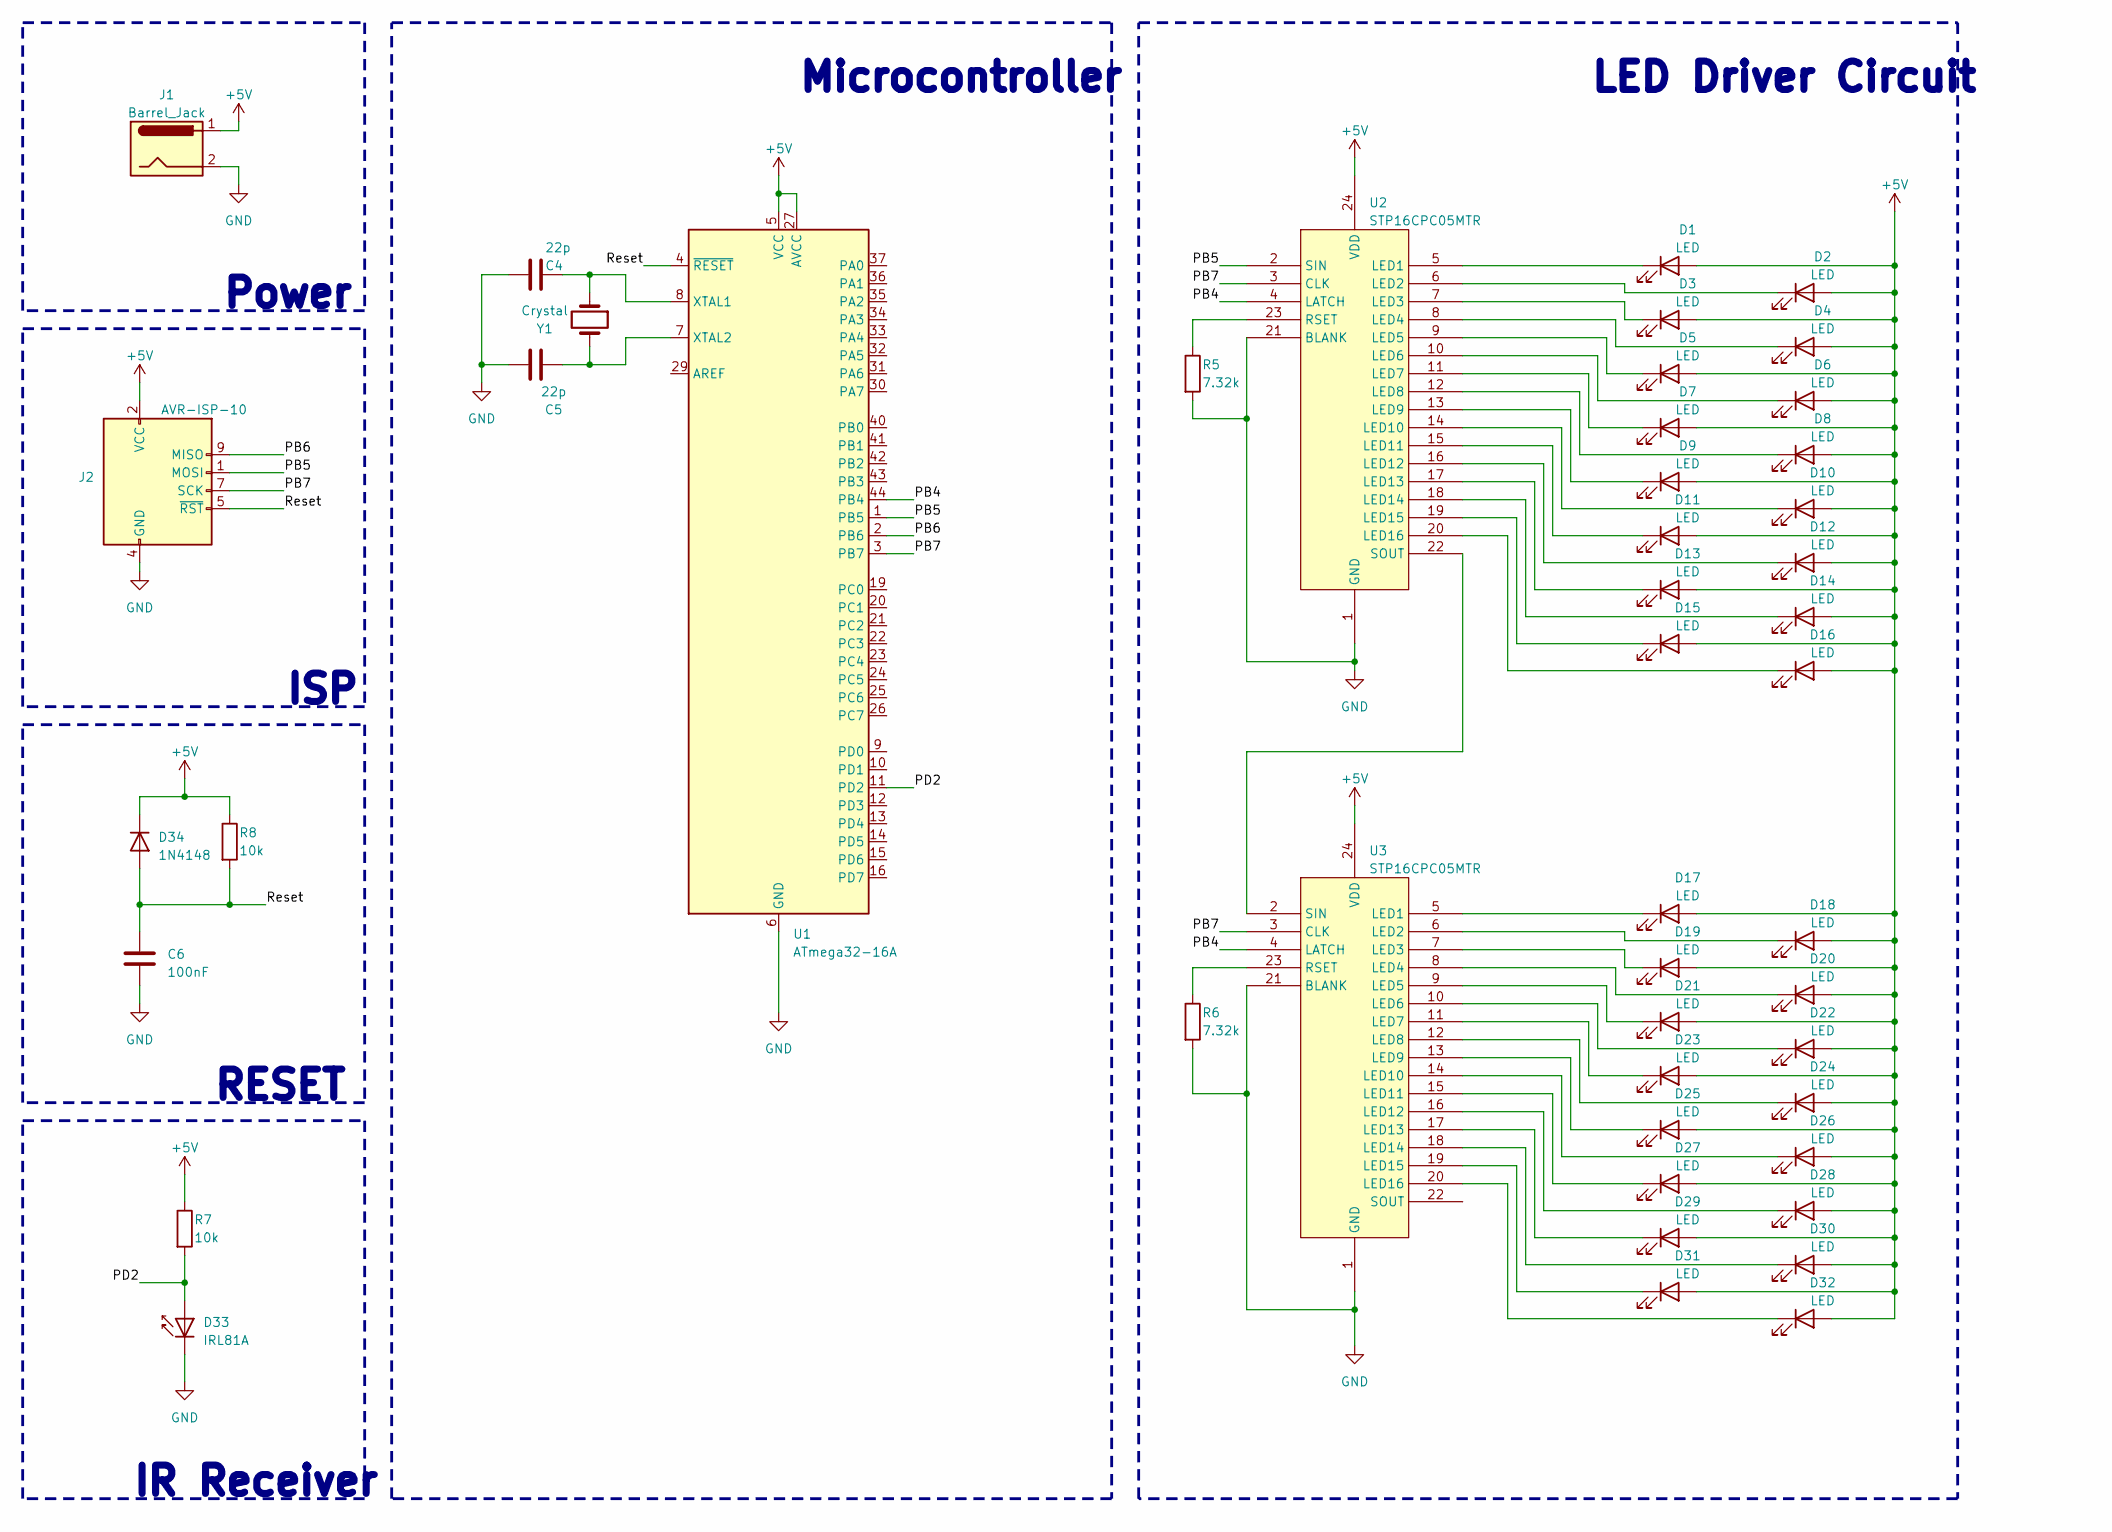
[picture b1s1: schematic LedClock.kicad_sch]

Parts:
C4, C5: 22p; C_0603_1608Metric
C6: 100nF; C_0603_1608Metric
D1, D2, D3, D4, D5, D6, D7, D8, D9, D10, D11, D12, D13, D14, D15, D16, D17, D18, D19, D20, D21, D22, D23, D24, D25, D26, D27, D28, D29, D30, D31, D32: LED; LED_1206_3216Metric
D33: IRL81A; LED_SideEmitter_Rectangular_W4.5mm_H1.6mm
D34: 1N4148; D_DO-35_SOD27_P7.62mm_Horizontal
J1: Barrel_Jack; JST_PH_S2B-PH-SM4-TB_1x02-1MP_P2.00mm_Horizontal
J2: AVR-ISP-10; ISP-10
R5, R6: 7.32k; R_0603_1608Metric
R7, R8: 10k; R_0603_1608Metric
U1: ATmega32-16A; TQFP-44_10x10mm_P0.8mm
U2, U3: STP16CPC05MTR; SOIC-24W_7.5x15.4mm_P1.27mm
Y1: Crystal; Crystal_HC49-4H_Vertical

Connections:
+5V: D1.2 (A), D2.2 (A), D3.2 (A), D4.2 (A), D5.2 (A), D6.2 (A), D7.2 (A), D8.2 (A), D9.2 (A), D10.2 (A), D11.2 (A), D12.2 (A), D13.2 (A), D14.2 (A), D15.2 (A), D16.2 (A), D17.2 (A), D18.2 (A), D19.2 (A), D20.2 (A), D21.2 (A), D22.2 (A), D23.2 (A), D24.2 (A), D25.2 (A), D26.2 (A), D27.2 (A), D28.2 (A), D29.2 (A), D30.2 (A), D31.2 (A), D32.2 (A), D34.1 (K), J1.1, J2.2 (VCC), R7.1, R8.1, U1.5 (VCC), U1.17 (VCC), U1.27 (AVCC), U1.38 (VCC), U2.24 (VDD), U3.24 (VDD)
/PB4: U1.44 (PB4), U2.4 (LATCH), U3.4 (LATCH)
/PB5: J2.1 (MOSI), U1.1 (PB5), U2.2 (SIN)
/PB6: J2.9 (MISO), U1.2 (PB6)
/PB7: J2.7 (SCK), U1.3 (PB7), U2.3 (CLK), U3.3 (CLK)
/PD2: D33.2 (A), R7.2, U1.11 (PD2)
/Reset: C6.1, D34.2 (A), J2.5 (~RST), R8.2, U1.4 (~RESET)
GND: C4.2, C5.2, C6.2, D33.1 (K), J1.2, J2.4 (GND), J2.6 (GND), J2.8 (GND), J2.10 (GND), R5.2, R6.2, U1.6 (GND), U1.18 (GND), U1.28 (GND), U1.39 (GND), U2.1 (GND), U2.21 (BLANK), U3.1 (GND), U3.21 (BLANK)
unnamed: D1.1 (K), U2.5 (LED1)
unnamed: D2.1 (K), U2.6 (LED2)
unnamed: D3.1 (K), U2.7 (LED3)
unnamed: D4.1 (K), U2.8 (LED4)
unnamed: D5.1 (K), U2.9 (LED5)
unnamed: D6.1 (K), U2.10 (LED6)
unnamed: D7.1 (K), U2.11 (LED7)
unnamed: D8.1 (K), U2.12 (LED8)
unnamed: D9.1 (K), U2.13 (LED9)
unnamed: D10.1 (K), U2.14 (LED10)
unnamed: D11.1 (K), U2.15 (LED11)
unnamed: D12.1 (K), U2.16 (LED12)
unnamed: D13.1 (K), U2.17 (LED13)
unnamed: D14.1 (K), U2.18 (LED14)
unnamed: D15.1 (K), U2.19 (LED15)
unnamed: D16.1 (K), U2.20 (LED16)
unnamed: D17.1 (K), U3.5 (LED1)
unnamed: D18.1 (K), U3.6 (LED2)
unnamed: D19.1 (K), U3.7 (LED3)
unnamed: D20.1 (K), U3.8 (LED4)
unnamed: D21.1 (K), U3.9 (LED5)
unnamed: D22.1 (K), U3.10 (LED6)
unnamed: D23.1 (K), U3.11 (LED7)
unnamed: D24.1 (K), U3.12 (LED8)
unnamed: D25.1 (K), U3.13 (LED9)
unnamed: D26.1 (K), U3.14 (LED10)
unnamed: D27.1 (K), U3.15 (LED11)
unnamed: D28.1 (K), U3.16 (LED12)
unnamed: D29.1 (K), U3.17 (LED13)
unnamed: D30.1 (K), U3.18 (LED14)
unnamed: D31.1 (K), U3.19 (LED15)
unnamed: D32.1 (K), U3.20 (LED16)
unnamed: C4.1, U1.8 (XTAL1), Y1.1
unnamed: C5.1, U1.7 (XTAL2), Y1.2
unnamed: R5.1, U2.23 (RSET)
unnamed: U2.22 (SOUT), U3.2 (SIN)
unnamed: R6.1, U3.23 (RSET)

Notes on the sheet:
Power
ISP
RESET
Microcontroller
LED Driver Circuit
IR Receiver

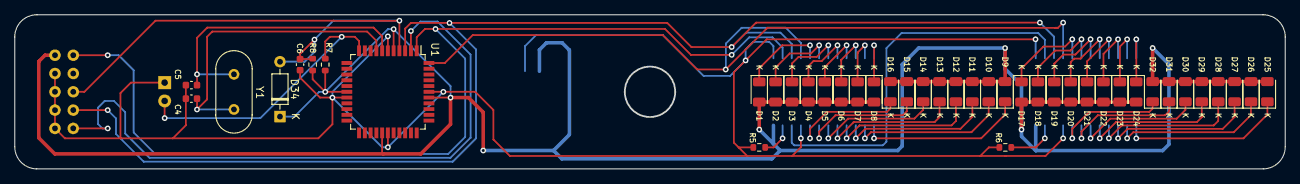
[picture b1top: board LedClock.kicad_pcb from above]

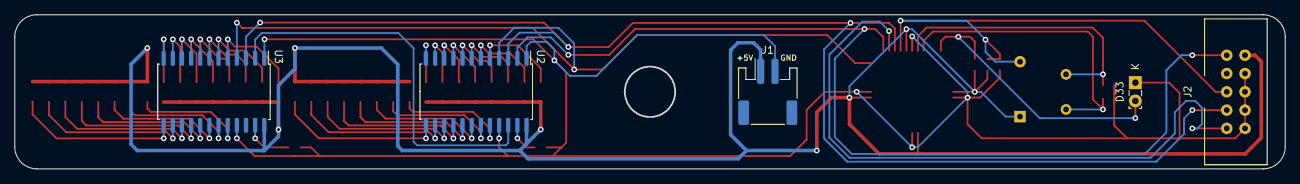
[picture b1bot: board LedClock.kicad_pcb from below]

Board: 2 copper layers, 176.4 x 21.4 mm, 47 parts (5 on the bottom side), 45 nets.

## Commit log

2021-11-09 .gitignore edited online with Bitbucket
2021-11-09 README.md edited online with Bitbucket
2021-11-09 images created online with Bitbucket
2021-11-09 images edited online with Bitbucket
2021-11-09 d created online with Bitbucket
2021-11-09 Adding project images.
2021-11-09 Add solution
2022-02-14 Adding Project Solution
2022-02-14 Fixed image path in ReadMe file
2023-04-16 Refactored the pov clock code. Updated images.
2023-04-16 added entire .vscode folder to git ignore
2023-04-16 Updated gitignore
2023-04-16 adding Attiny pwm project
2023-04-16 Removed Parts List. Renamed images. Updated Readme.
2023-04-16 Fixed issue with image src paths in readme file. Removed underscores from image names and added hyphens.
2023-04-16 Updated image sizes in readme file.
2023-04-16 Updated Image placement on readme file
2023-04-16 Updated clock image
2023-04-16 Updated gitignore to include kicad ignore files
2023-04-16 Updated gitignore to ignore kicad backup folder
2023-04-16 adding kicad project
2023-04-16 Updated image style on readme file
2023-04-16 update image styles in readme file
2023-04-16 Updated image sizes
2023-04-16 Update image sizes in readme file
2023-04-16 Added led-circuit-schematic
2023-04-16 Updated readme html
2023-04-16 updated headings on readme file
2023-04-16 Updated readme file
2023-04-17 Added updated video demonstration link
2023-04-17 Updated video demonstration link
2023-04-17 Fixed issue with demonstration link
2023-04-22 Refactored code and added documentation comments.
2023-04-22 Refactored code
2023-04-22 Refactored code.
2023-04-23 Adding platformIo pov-clock project. Removed atmel project
2023-04-29 Refactored clock animation code
2023-05-27 Connected AVCC to the 5 volts rail.
2023-06-12 Updated comments and refactored the draw clock function.
2023-06-12 Fixed bug in the configureInput function and updated comments.
2023-10-07 Refactored code - Renamed functions - Removed unneccessary variables - Added comments
2023-10-07 Updated comments for esc driver code
2023-10-07 Corrected Comment
2023-10-08 Added comments
2023-10-09 Updated comments and renamed files
2023-10-10 Updated comments
2023-10-11 - Created an entire clock image data multidimensional array - Update comments
2023-10-16 - Updated image of the led circuit schematic - Created an esc driver kicad file - Added an immage of the esc driver circuit
2023-10-16 - updated the esc driver kicad file directory
2023-10-16 - Added the esc driver circuit image to the readme file
2023-10-16 Update esc schematic file extension
2023-10-16 - Added ir transmitter to the esc driver circuit. - Updated readme file
2023-10-16 - corrected file extension in readme file
2023-10-16 - updated teh esc drive circuit schematic
2023-10-18 - Updated folder struction of the repo - Created an eda folder that holds KiCad files - Created a software folder that holds the microcontroller programs. - Moved everything into the appropriate fold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
2023-10-18 - removed .pio directory from gitignore
2023-10-18 - Added .pio directory back to git ignore
2023-10-18 - Added case files - Added image of the clock powered - Updated readme file
2023-10-18 Updated video size
2023-10-18 - centered video image
2023-10-18 - Updated readme
2023-10-18 - Updated read me
2023-10-19 - added the progmem modifier to the clock image data - used pgm_read_byte to access the clockImageData
2023-10-19 - updated readme file
2023-10-19 - dual table test readme
2023-10-19 - Updated parts list in read
2023-10-19 - updated parts list
2023-10-19 -updated readme
2023-10-19 - updated parts l ist
2023-10-20 updated parts list
2023-10-20 - updpated readme
2023-10-21 Update README.md
    Update the esc circuit description in the readme file
2023-10-21 Update README.md
    Updated the PWM Overview section of the readme file
2023-10-21 Update README.md
    - Updated images in readme file
2023-10-21 - Aded new image of the case
2023-10-21 Update README.md
    - Updated image position in readme file
2023-10-21 - updated image size in the readme file
2023-10-21 - updated image sizes in the readme file
2023-10-21 Update README.md
    - updated image size in readme file
2023-10-21 Update README.md
    - updated image sizes in readme file
2023-10-21 Update README.md
    - removed description sections in read me file
2023-10-21 Update README.md
    - Updated the timer section of the readme file
2023-10-21 - Fixed comments
2023-10-21 Update README.md
    - updated the LED drivers section on the readme file
2023-10-21 Update README.md
    - updated led driver section of the readme file
2023-10-21 Update README.md
    - Updated the led driver table in the readme file
2023-10-21 Update README.md
    - Updated led driver table in the readme file
2023-10-21 Update README.md
    - added dividers between sub sections in readme file
2023-10-21 - renamed case stl file
2023-10-21 Update README.md
    - added case stl to readme file
2023-10-21 Update README.md
    - added stl ascii for the case to the readme file
2023-10-21 - added new image of the finished clock
2023-10-21 - modified images
2023-10-21 Update README.md
    - replaced the led clock image in the readme file
2023-10-21 - added a divered between the schematics in the readme file
2023-10-21 - fixed divider in thre readme file
2023-10-21 Update README.md
    - Removed overview section
    - Fixed VRDude typo
2023-10-21 Update README.md
    - Added a power consumption table to the readme file
2023-10-21 Update README.md
    - renamed the powersupply link in the readme file
2023-10-21 - Fixed escschematic link in the readme file
2023-10-21 Update README.md
    - fixed part list table format in the readme file
2023-10-21 - fixed youtube demo link in the readme file
2023-10-21 - updated PWM overview in the readme file
2023-10-21 - fixed type on readme file
2023-10-23 - Added new animation to the clock
2024-02-09 Uploading MIT License-
